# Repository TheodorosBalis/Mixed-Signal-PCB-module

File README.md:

# Mixed-Signal PCB Module

A four-layer KiCad 9 PCB design for a compact GSM/GPRS handheld device. It combines a Quectel M95 cellular module, an STM32 microcontroller, battery charging and regulation, a SIM interface, display connector, keypad, and audio circuitry.

## Design specifications

| Item | Implemented design |
| --- | --- |
| Board outline | 46 x 100 mm |
| Copper layers | 4: `F.Cu`, `In1.Cu`, `In2.Cu`, `B.Cu` |
| Stackup material | FR-4 dielectrics; ENIG finish specified in KiCad |
| Board thickness | 2.9984 mm as currently stored in the PCB file; confirm with the fabricator |
| Cellular module | Quectel M95 GSM/GPRS (`U1`) |
| MCU | STM32G030K6Tx (`U2`) |
| Power | BQ24166RGE charger/power-path IC (`U4`), 3.3 V regulator (`U3`), Micro-USB power input (`J3`), battery connector (`J1`) |
| RF interface | U.FL coaxial connector (`J6`) for an external antenna; 0-ohm series link (`R5`) and DNP shunt matching positions (`C16`, `C17`) |
| Display | 12-position, 0.5 mm-pitch FPC connector (`J4`) for the intended ST7789-based 240 x 240 LCD module |
| SIM | Nano-SIM connector (`J5`) with interface protection |
| User I/O | 20 keypad switches, status LEDs, microphone, speaker |
| Programming/debug | Tag-Connect SWD connector (`J2`); SWO is not connected |
| Mechanical | Four 2 mm mounting-hole footprints |

The Micro-USB connector is used for power; its USB data pins are unconnected in this design. The U.FL connector is **not** an antenna: an appropriate external antenna and cable are required for RF operation.

## Repository files

- `mixedsignalBoard.kicad_pro` - KiCad project settings.
- `mixedsignalBoard.kicad_sch` - circuit schematic.
- `mixedsignalBoard.kicad_pcb` - PCB layout, footprints, routing, and board stackup.

Open `mixedsignalBoard.kicad_pro` with KiCad 9 to inspect the schematic and layout. Firmware, manufacturing exports, assembly files, and a physical antenna are not included in this repository.

## Before fabrication

This is a design project, not a validated hardware product. Check the actual LCD module pinout and connector orientation, antenna matching and 50-ohm RF geometry against the chosen fabricator's stackup, and all component part numbers before ordering. The PCB currently assigns both inner copper zones to `M95_SIM_GND` and records an approximately 3.0 mm stackup; verify that these are intentional and manufacturable. Passing ERC or DRC alone does not establish electrical, RF, or functional performance.

## Design gallery

The views below show the system block diagram, complete schematic, PCB routing, and both sides of the board. The 3D images are KiCad renders, not photographs of fabricated hardware.

### System block diagram

The diagram summarizes power distribution and the connections between the STM32, M95, display, keypad, SIM, RF, and audio circuits.

[High-resolution PNG](images/mixed-signal-block-diagram.png) | [Editable SVG](images/mixed-signal-block-diagram.svg)

### Schematic

### PCB layout

| Front copper view | Multi-layer routing view |
| --- | --- |
|  |  |

### 3D renders

| Component side | Keypad side |
| --- | --- |
|  |  |

| Perspective view | Board edge profile |
| --- | --- |
|  |  |

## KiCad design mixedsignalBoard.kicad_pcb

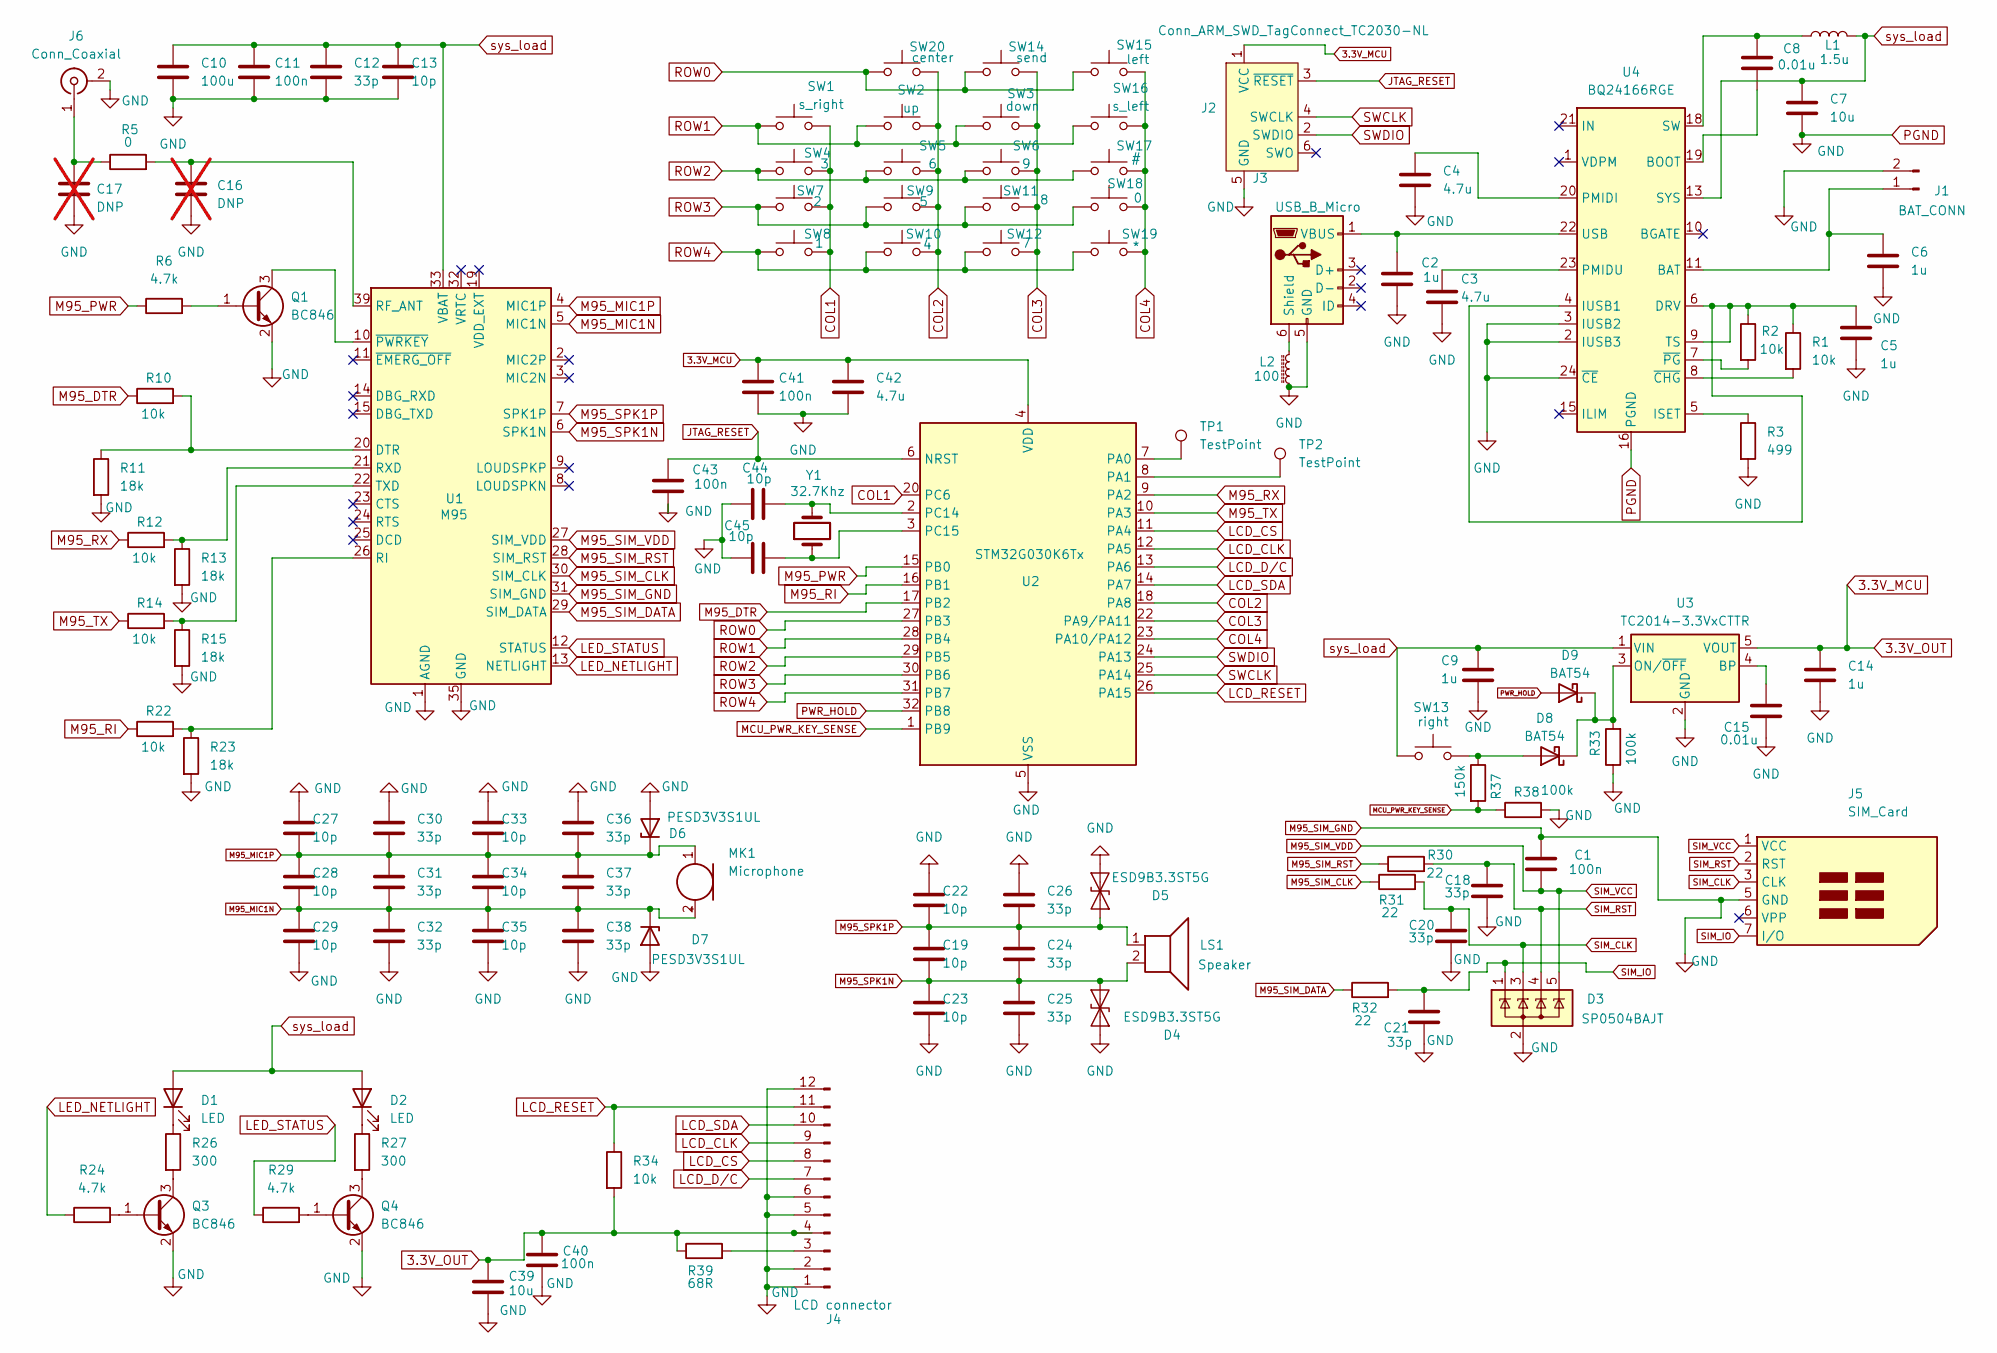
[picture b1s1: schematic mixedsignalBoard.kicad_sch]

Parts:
C1, C11, C40, C41: 100n; C_0402_1005Metric
C2, C5, C6, C9, C14: 1u; C_0805_2012Metric
C3, C4, C42: 4.7u; C_0603_1608Metric
C7, C39: 10u; C_0805_2012Metric
C8, C15: 0.01u; C_0402_1005Metric
C10: 100u; CP_EIA-3216-18_Kemet-A
C12, C18, C20, C21, C24, C25, C26, C30, C31, C32, C36, C37, C38: 33p; C_0402_1005Metric
C13, C44, C45: 10p; C_0402_1005Metric
C16, C17: DNP; C_0402_1005Metric; not fitted
C19, C22, C23, C27, C28, C29, C33, C34, C35: 10p; C_0603_1608Metric
C43: 100n; C_0805_2012Metric
D1, D2: LED; LED_0603_1608Metric
D3: SP0504BAJT; SOT-353_SC-70-5
D4, D5: ESD9B3.3ST5G; D_SOD-923
D6, D7: PESD3V3S1UL; D_SOD-882
D8, D9: BAT54; D_SOD-323
J1: BAT_CONN; JST_PH_S2B-PH-K_1x02_P2.00mm_Horizontal
J2: Conn_ARM_SWD_TagConnect_TC2030-NL; Tag-Connect_TC2030-IDC-NL_2x03_P1.27mm_Vertical
J3: USB_B_Micro; USB_Micro-B_Molex_47346-0001
J4: LCD connector; Hirose_FH12-12S-0.5SH_1x12-1MP_P0.50mm_Horizontal
J5: SIM_Card; nanoSIM_Hinged_CUI_NSIM-2-C
J6: Conn_Coaxial; U.FL_Hirose_U.FL-R-SMT-1_Vertical
L1: 1.5u; L_2010_5025Metric
L2: 100; L_0603_1608Metric
LS1: Speaker; Speaker_CUI_CMR-1206S-67
MK1: Microphone; CUI_CMC-4013-SMT
Q1, Q3, Q4: BC846; SOT-23
R1, R2, R10, R14, R22, R34: 10k; R_0603_1608Metric
R3: 499; R_0603_1608Metric
R5: 0; R_0402_1005Metric
R6, R24, R29: 4.7k; R_0402_1005Metric
R11, R13, R15, R23: 18k; R_0603_1608Metric
R12: 10k; R_0201_0603Metric
R26, R27: 300; R_0402_1005Metric
R30, R31, R32: 22; R_0402_1005Metric
R33, R38: 100k; R_0201_0603Metric
R37: 150k; R_0201_0603Metric
R39: 68R; R_0603_1608Metric
SW1: s_right; membrane_switch_4.4mm_V2
SW2: up; membrane_switch_4.4mm_V2
SW3: down; membrane_switch_4.4mm_V2
SW4: 3; membrane_switch_4.4mm_V2
SW5: 6; membrane_switch_4.4mm_V2
SW6: 9; membrane_switch_4.4mm_V2
SW7: 2; membrane_switch_4.4mm_V2
SW8: 1; membrane_switch_4.4mm_V2
SW9: 5; membrane_switch_4.4mm_V2
SW10: 4; membrane_switch_4.4mm_V2
SW11: 8; membrane_switch_4.4mm_V2
SW12: 7; membrane_switch_4.4mm_V2
SW13: right; membrane_switch_4.4mm_V2
SW14: send; membrane_switch_4.4mm_V2
SW15: left; membrane_switch_4.4mm_V2
SW16: s_left; membrane_switch_4.4mm_V2
SW17: #; membrane_switch_4.4mm_V2
SW18: 0; membrane_switch_4.4mm_V2
SW19: *; membrane_switch_4.4mm_V2
SW20: center; membrane_switch_4.4mm_V2
TP1, TP2: TestPoint; TestPoint_Pad_D1.0mm
U1: M95; Quectel_M95
U2: STM32G030K6Tx; LQFP-32_7x7mm_P0.8mm
U3: TC2014-3.3VxCTTR; SOT-23-5
U4: BQ24166RGE; Texas_RGE0024H_VQFN-24-1EP_4x4mm_P0.5mm_EP2.7x2.7mm
Y1: 32.7Khz; Crystal_SMD_3215-2Pin_3.2x1.5mm

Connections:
3.3V_MCU: C14.1, C39.1, C40.1, C41.1, C42.1, J2.1 (VCC), J4.4 (VDD), R34.2, R39.1, U2.4 (VDD), U3.5 (VOUT)
COL1: SW1.2, SW4.2, SW7.2, SW8.2, U2.20 (PC6)
COL2: SW2.2, SW5.2, SW9.2, SW10.2, SW20.2, U2.18 (PA8)
COL3: SW3.2, SW6.2, SW11.2, SW12.2, SW14.2, U2.22 (PA9/PA11)
COL4: SW15.2, SW16.2, SW17.2, SW18.2, SW19.2, U2.23 (PA10/PA12)
JTAG_RESET: C43.1, J2.3 (~RESET), U2.6 (NRST)
LCD_CLK: J4.9 (SCL), U2.12 (PA5)
LCD_CS: J4.8 (CS), U2.11 (PA4)
LCD_D/C: J4.7 (D/C), U2.13 (PA6)
LCD_RESET: J4.11 (RESET), R34.1, U2.26 (PA15)
LCD_SDA: J4.10 (SDA), U2.14 (PA7)
LED_NETLIGHT: R24.1, U1.13 (NETLIGHT)
LED_STATUS: R29.1, U1.12 (STATUS)
M95_DTR: R10.1, U2.17 (PB2)
M95_MIC1N: C28.2, C29.1, C31.2, C32.1, C34.2, C35.1, C37.2, C38.1, D7.1 (K), MK1.2 (+), U1.5 (MIC1N)
M95_MIC1P: C27.2, C28.1, C30.2, C31.1, C33.2, C34.1, C36.2, C37.1, D6.1 (K), MK1.1 (-), U1.4 (MIC1P)
M95_PWR: R6.1, U2.15 (PB0)
M95_RI: R22.1, U2.16 (PB1)
M95_RX: R12.1, U2.9 (PA2)
M95_SIM_CLK: R31.1, U1.30 (SIM_CLK)
M95_SIM_DATA: R32.1, U1.29 (SIM_DATA)
M95_SIM_GND: C1.1, C2.2, C3.2, C4.2, C5.2, C6.2, C7.2, C9.2, C10.2, C11.2, C12.2, C13.2, C14.2, C15.2, C16.2, C17.2, C18.2, C20.2, C21.2, C22.1, C23.2, C25.2, C26.1, C27.1, C29.2, C30.1, C32.2, C33.1, C35.2, C36.1, C38.2, C39.2, C40.2, C41.2, C42.2, C43.2, C44.1, C45.1, D3.2 (A), D4.1 (A1), D5.2 (A2), D6.2 (A), D7.2 (A), J1.2, J2.5 (GND), J3.5 (GND), J4.1 (GND), J4.2 (LEDK), J4.5 (GND), J4.6 (GND), J4.12 (GND), J5.5 (GND), J6.2 (Ext), L2.1, Q1.2 (E), Q3.2 (E), Q4.2 (E), R3.2, R11.2, R13.2, R15.2, R23.2, R33.1, R38.2, U1.1 (AGND), U1.31 (SIM_GND), U1.35 (GND), U1.36 (GND), U1.37 (GND), U1.38 (GND), U1.40 (GND), U2.5 (VSS), U3.2 (GND), U4.2 (IUSB3), U4.3 (IUSB2), U4.16 (PGND), U4.17 (PGND), U4.24 (~CE), U4.25 (PGND)
M95_SIM_RST: R30.1, U1.28 (SIM_RST)
M95_SIM_VDD: C1.2, D3.5 (K), J5.1 (VCC), U1.27 (SIM_VDD)
M95_SPK1N: C19.2, C23.1, C24.2, C25.1, D4.2 (A2), LS1.2, U1.6 (SPK1N)
M95_SPK1P: C19.1, C22.2, C24.1, C26.2, D5.1 (A1), LS1.1, U1.7 (SPK1P)
M95_TX: R14.1, U2.10 (PA3)
MCU_PWR_KEY_SENSE: R37.2, R38.1, U2.1 (PB9)
unnamed: D1.1 (K), R26.1
unnamed: D2.1 (K), R27.1
unnamed: D8.2 (A), R37.1, SW13.2
unnamed: D8.1 (K), D9.1 (K), R33.2, U3.3 (ON/~OFF)
unnamed: C6.1, J1.1, U4.11 (BAT), U4.12 (BAT)
unnamed: J3.6 (Shield), L2.2
unnamed: C2.1, J3.1 (VBUS), U4.22 (USB)
unnamed: J4.3 (LEDA), R39.2
unnamed: C17.1, J6.1 (In), R5.1
unnamed: Q1.1 (B), R6.2
unnamed: Q1.3 (C), U1.10 (~PWRKEY)
unnamed: Q3.1 (B), R24.2
unnamed: Q3.3 (C), R26.2
unnamed: Q4.1 (B), R29.2
unnamed: Q4.3 (C), R27.2
unnamed: R10.2, R11.1, U1.20 (DTR)
unnamed: C16.1, R5.2, U1.39 (RF_ANT)
unnamed: R22.2, R23.1, U1.26 (RI)
unnamed: R12.2, R13.1, U1.21 (RXD)
unnamed: R14.2, R15.1, U1.22 (TXD)
unnamed: TP1.1, U2.7 (PA0)
unnamed: TP2.1, U2.8 (PA1)
unnamed: C44.2, U2.2 (PC14), Y1.2
unnamed: C45.2, U2.3 (PC15), Y1.1
unnamed: C15.1, U3.4 (BP)
unnamed: C8.2, U4.19 (BOOT)
unnamed: C5.1, R1.1, R2.1, U4.4 (IUSB1), U4.6 (DRV), U4.9 (TS)
unnamed: R3.1, U4.5 (ISET)
unnamed: C4.1, U4.20 (PMIDI)
unnamed: C3.1, U4.23 (PMIDU)
unnamed: C8.1, L1.1, U4.18 (SW)
unnamed: R1.2, U4.8 (~CHG)
unnamed: R2.2, U4.7 (~PG)
PWR_HOLD: D9.2 (A), U2.32 (PB8)
ROW0: SW14.1, SW15.1, SW20.1, U2.27 (PB3)
ROW1: SW1.1, SW2.1, SW3.1, SW16.1, U2.28 (PB4)
ROW2: SW4.1, SW5.1, SW6.1, SW17.1, U2.29 (PB5)
ROW3: SW7.1, SW9.1, SW11.1, SW18.1, U2.30 (PB6)
ROW4: SW8.1, SW10.1, SW12.1, SW19.1, U2.31 (PB7)
SIM_CLK: C20.1, D3.3 (K), J5.3 (CLK), R31.2
SIM_IO: C21.1, D3.1 (K), J5.7 (I/O), R32.2
SIM_RST: C18.1, D3.4 (K), J5.2 (RST), R30.2
SWCLK: J2.4 (SWCLK), U2.25 (PA14)
SWDIO: J2.2 (SWDIO), U2.24 (PA13)
sys_load: C7.1, C9.1, C10.1, C11.1, C12.1, C13.1, D1.2 (A), D2.2 (A), L1.2, SW13.1, U1.33 (VBAT), U1.34 (VBAT), U3.1 (VIN), U4.13 (SYS), U4.14 (SYS)

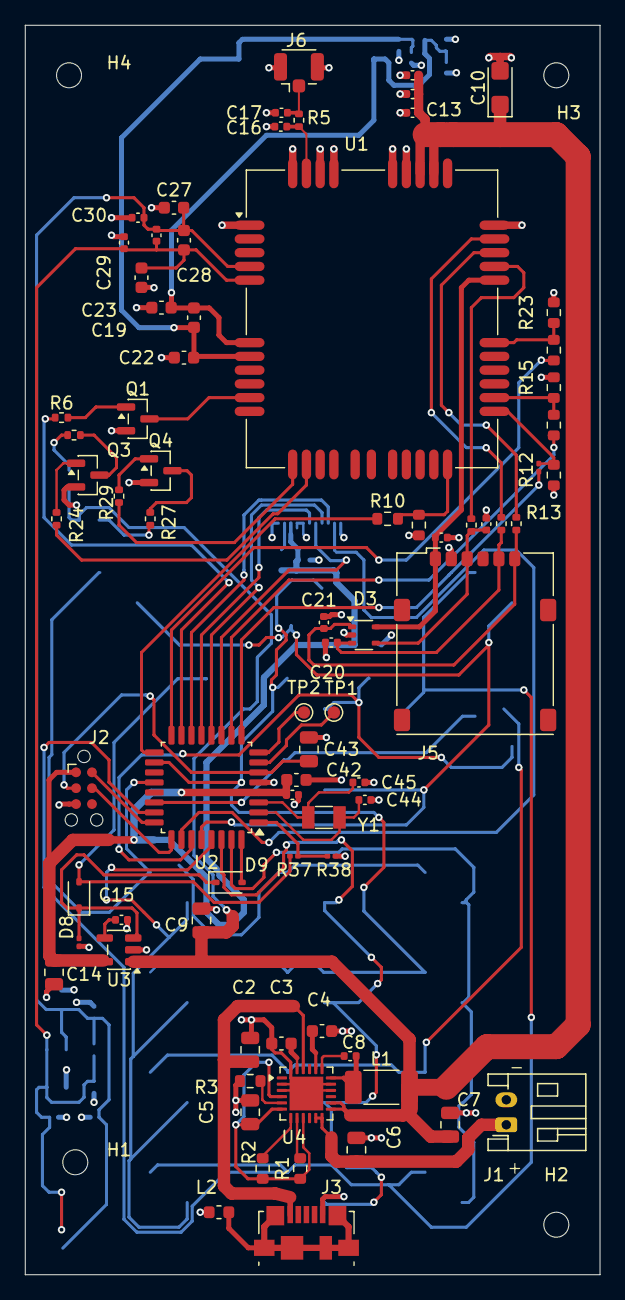
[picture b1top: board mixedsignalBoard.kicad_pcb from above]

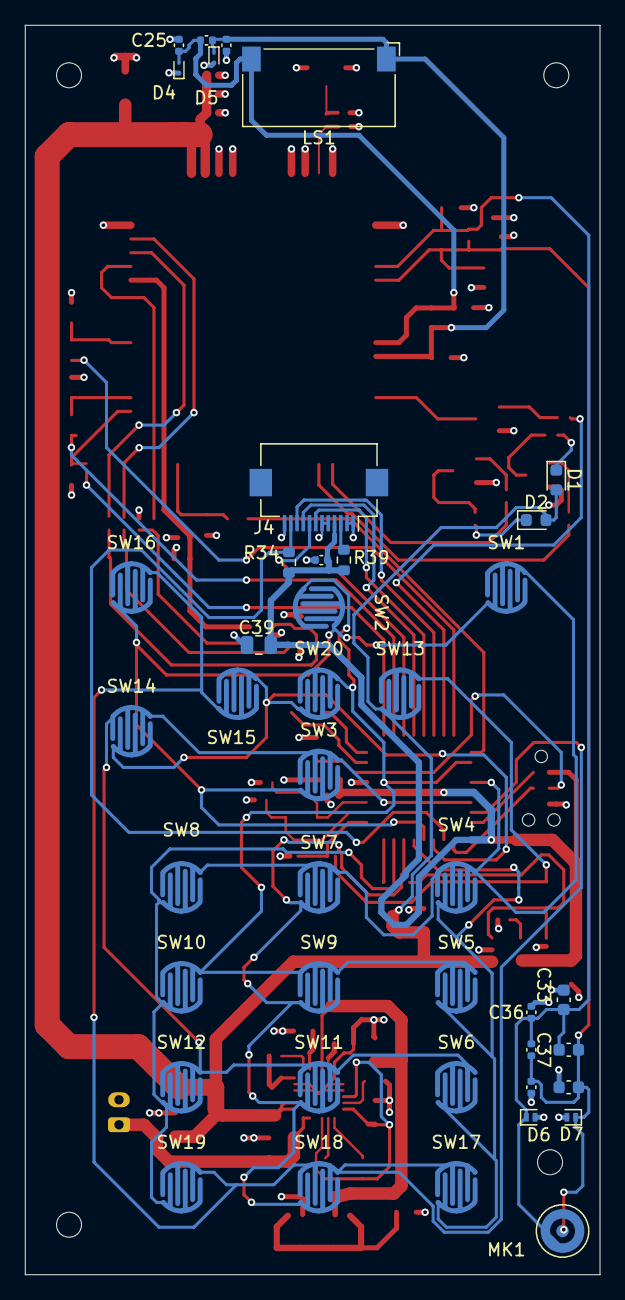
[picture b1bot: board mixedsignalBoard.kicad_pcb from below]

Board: 4 copper layers, 46.0 x 100.0 mm, 123 parts (42 on the bottom side), 73 nets.

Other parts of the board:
H1, H2, H3, H4: MountingHole_2mm
